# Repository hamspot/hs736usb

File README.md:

# Ham Spot Inc
##  HS-736USB
http://hamspot.com/33-prod-hs-736usb

### FT-736R to HRD USB Interface
The Yaesu FT-736R remains a popular satellite ground station transceiver.  However some modern computer software is not compatible with the CAT interface on the FT-736R.  Ham Radio Deluxe, in particular, does not support the FT-736R.  Ham Radio Deluxe does support the Yaesu FT-847 which has similar features.  We can solve this incompatibility by programming a CAT interface to present a FT-847 to the PC and emulate the new commands not supported on the FT-736R.  

Features not present on the FT-736R are ignored.  Memory channels are not supported and the radio must be set to VFO, also satellite mode must be set to VFO, before enabling CAT control of the radio.  1240 MHz is mapped to 240 MHz because the FT-847 does not have 4 MHz digits.

### Credits
A short history, archived Comcast pages, and the original downloads are in **[Archives/README.md](Archives/README.md)**.

The concept was developed by Dave, KA6BFB in 2010 (Windows VB proof of concept, virtual serial ports): [Archives/Software.md](Archives/Software.md).

The hardware version was developed by Chuck, N6BIL (PIC18F14K50, GPL source and Eagle CAD): [Archives/Hardware.md](Archives/Hardware.md).

Ham Spot Inc based the HS-736USB on their great work and thanks them immensely for their hard work on solving a challenging problem! The goal of Ham Spot Inc is that if this interface is popular we will develop similar interfaces for other older rigs which are also not supported by HRD. Specifically in mind are the FT-757GXII, FT-890 and various Icom and Kenwood radios. There will likely be firmware updates to this hardware available on the http://hamspot.com/ website in the future. If you have a PIC programmer the chip has been socketed to allow you to flash new firmware or easily replace the device. If not, there will be made available an inexpensive preprogrammed chip that you can plugin to upgrade the firmware or convert the FT-736USB to another model Yaesu rig as they become supported.

### Arduino / ATmega328P port

An Arduino Uno/Nano port of the CAT translator lives in **[Arduino/](Arduino/)**. It keeps the PIC 847↔736 mapping, adds native-736 passthrough (pin A1 or a CAT opcode), PTT/band GPIO, and an S-meter PWM. The PIC firmware in `Firmware/` is unchanged.

```
arduino-cli compile --fqbn arduino:avr:nano Arduino/firmware
cd Arduino && test/run_suite.sh
```

See `Arduino/README.md`, `Arduino/docs/WIRING.md`, and `Arduino/docs/PROTOCOLS.md`. Operating manuals for both the PIC cabinet and the Arduino port are in [`Manual/`](Manual/).

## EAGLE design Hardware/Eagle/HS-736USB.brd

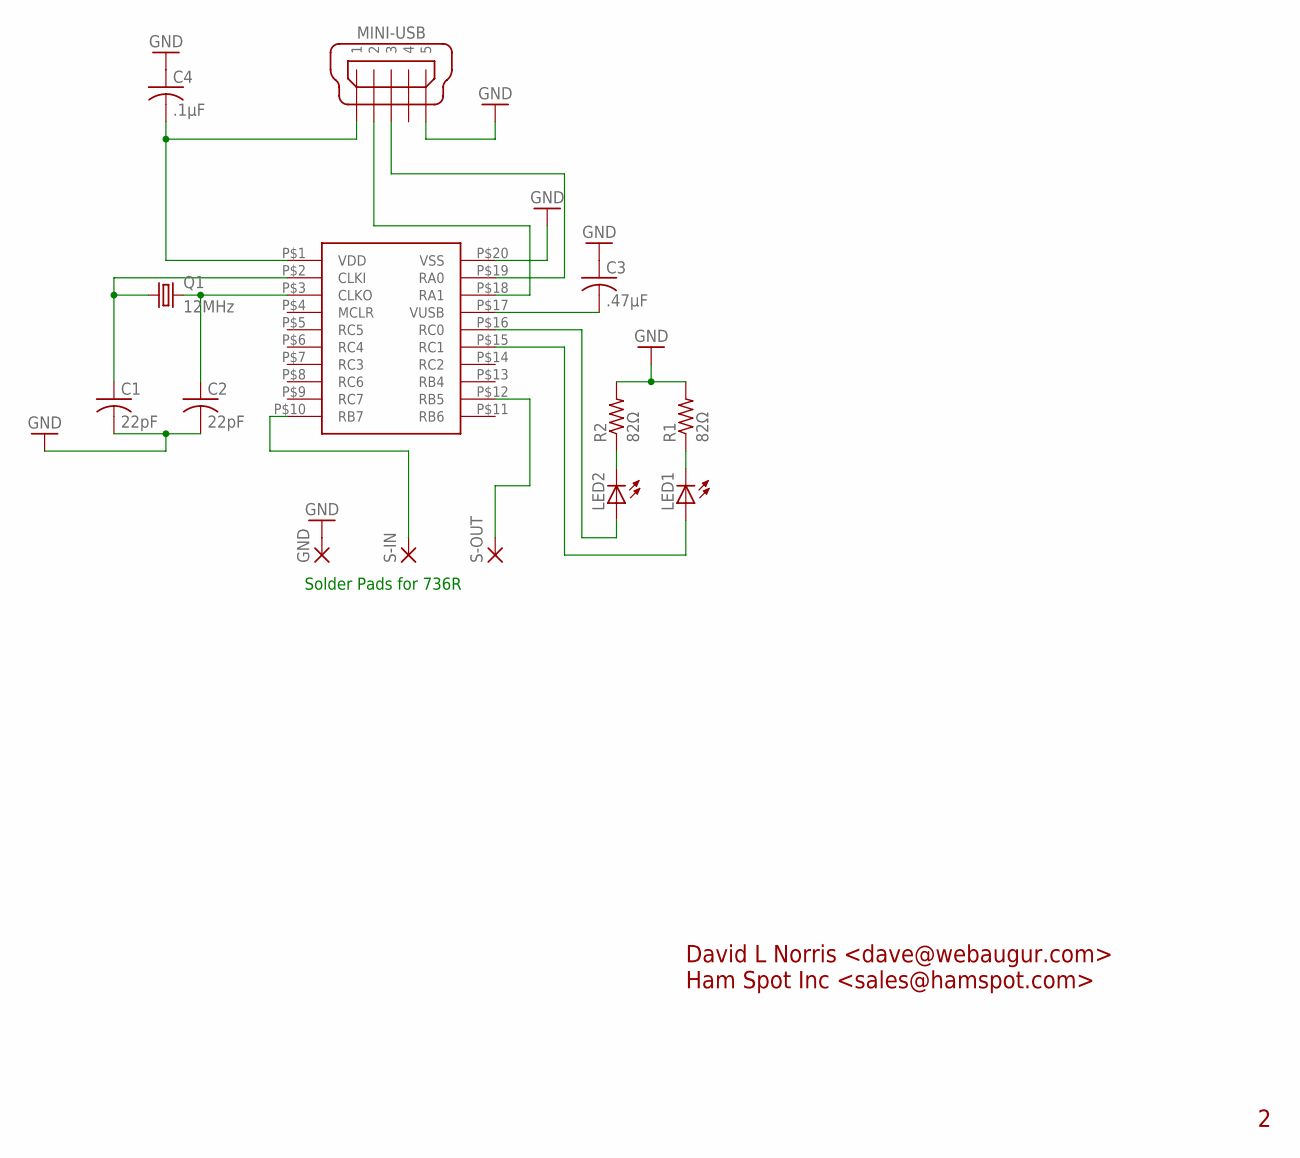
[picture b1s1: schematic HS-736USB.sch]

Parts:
C1, C2: 22pF; C1206
C3: .47µF; C1206
C4: .1µF; C1206
GND: 3,17/1,3
LED1, LED2: LED5MM
MINI-USB: MINI-USB-UX60-MB-5ST; UX60-MB-5ST
Q1: 12MHz; HC49/S
R1, R2: 82Ω; 0204V
S-IN: 3,17/1,3
S-OUT: 3,17/1,3
U$1: 14K50_DIP

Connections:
GND: C1.2, C2.2, C3.1, C4.1, GND.1, MINI-USB.5, R1.2, R2.2, U$1.P$20 (VSS)
unnamed: C2.1, Q1.2, U$1.P$3 (CLKO)
unnamed: C1.1, Q1.1, U$1.P$2 (CLKI)
unnamed: LED2.K (C), R2.1
unnamed: C4.2, MINI-USB.1, U$1.P$1 (VDD)
unnamed: LED1.K (C), R1.1
unnamed: C3.2, U$1.P$17 (VUSB)
unnamed: MINI-USB.2, U$1.P$18 (RA1)
unnamed: MINI-USB.3, U$1.P$19 (RA0)
unnamed: S-OUT.1, U$1.P$12 (RB5)
unnamed: S-IN.1, U$1.P$10 (RB7)
unnamed: LED2.A, U$1.P$16 (RC0)
unnamed: LED1.A, U$1.P$15 (RC1)

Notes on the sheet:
Solder Pads for 736R
David L Norris <dave@webaugur.com> Ham Spot Inc <sales@hamspot.com>

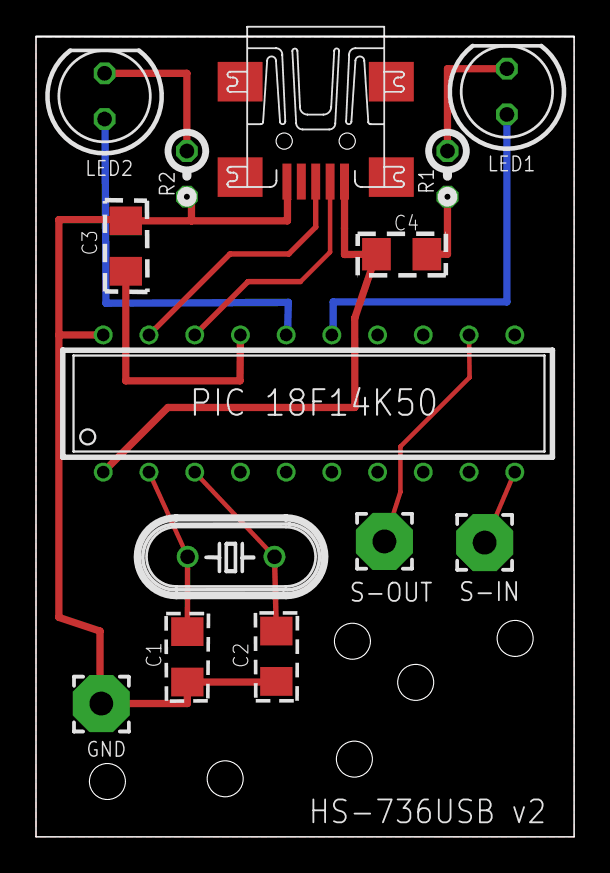
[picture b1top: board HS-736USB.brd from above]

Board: 2 copper layers, 29.9 x 44.5 mm, 14 parts (0 on the bottom side), 13 nets.

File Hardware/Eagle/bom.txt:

"Part";"Value";"Device";"Package";"Description";"";
"C1";"22pF";"C-USC1206";"C1206";"CAPACITOR, American symbol";"";
"C2";"22pF";"C-USC1206";"C1206";"CAPACITOR, American symbol";"";
"C3";".47µF";"C-USC1206";"C1206";"CAPACITOR, American symbol";"";
"C4";".1µF";"C-USC1206";"C1206";"CAPACITOR, American symbol";"";
"GND";"";"3,17/1,3";"3,17/1,3";"THROUGH-HOLE PAD";"";
"LED1";"";"LED5MM";"LED5MM";"LED";"";
"LED2";"";"LED5MM";"LED5MM";"LED";"";
"MINI-USB";"MINI-USB-UX60-MB-5ST";"MINI-USB-UX60-MB-5ST";"UX60-MB-5ST";"MINI USB Connector";"";
"Q1";"12MHz";"CRYSTALHC49S";"HC49/S";"CRYSTAL";"";
"R1";"82Ω";"R-US_0204/2V";"0204V";"RESISTOR, American symbol";"";
"R2";"82Ω";"R-US_0204/2V";"0204V";"RESISTOR, American symbol";"";
"S-IN";"";"3,17/1,3";"3,17/1,3";"THROUGH-HOLE PAD";"";
"S-OUT";"";"3,17/1,3";"3,17/1,3";"THROUGH-HOLE PAD";"";
"U$1";"14K50_DIP";"14K50_DIP";"14K50_DIP";"14K50 20pin dip";"";

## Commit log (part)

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2015-02-02 Initial Import of Ham Spot HS-736USB Source Code and Hardware Design Files. Version 1.0 hardware interface.
2015-02-02 Added makercase.com cabinet plans. Dimension only. AI/SVG files will later include holes for USB, cable, LEDs, etc.
2015-02-02 Added USB status LED indicators to the schematic and board layout. Refactored the silkscreen layers to be less cluttered and within boundaries.
2016-08-18 Updated schematic and board for a small board run August 2016. Added missing Artwork for the various enclosure designs and board renderings.
2016-08-18 Moved files around to the appropriate folders.
2016-08-18 Moved renderings into appropriate folders.
2016-08-18 Updated readme for cabinet files.

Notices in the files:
Hardware/Eagle/HS-736USB.brd:
Copyright 2011 Albert Jones
Copyright 2015 Ham Spot Inc
